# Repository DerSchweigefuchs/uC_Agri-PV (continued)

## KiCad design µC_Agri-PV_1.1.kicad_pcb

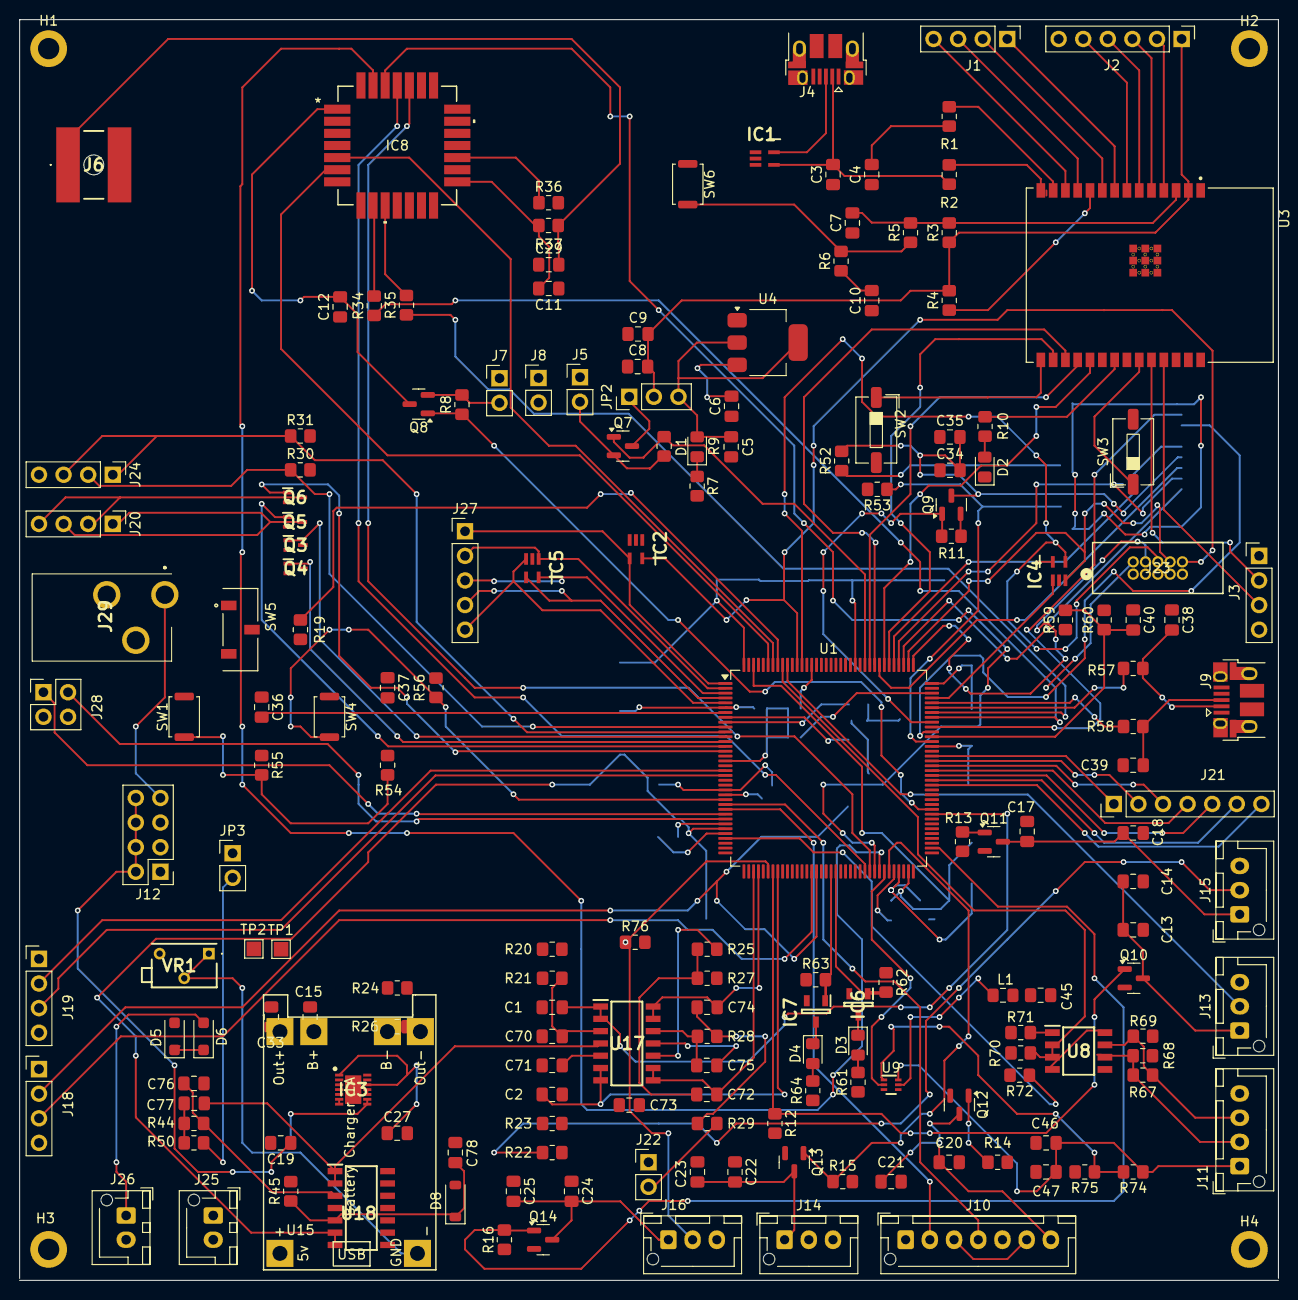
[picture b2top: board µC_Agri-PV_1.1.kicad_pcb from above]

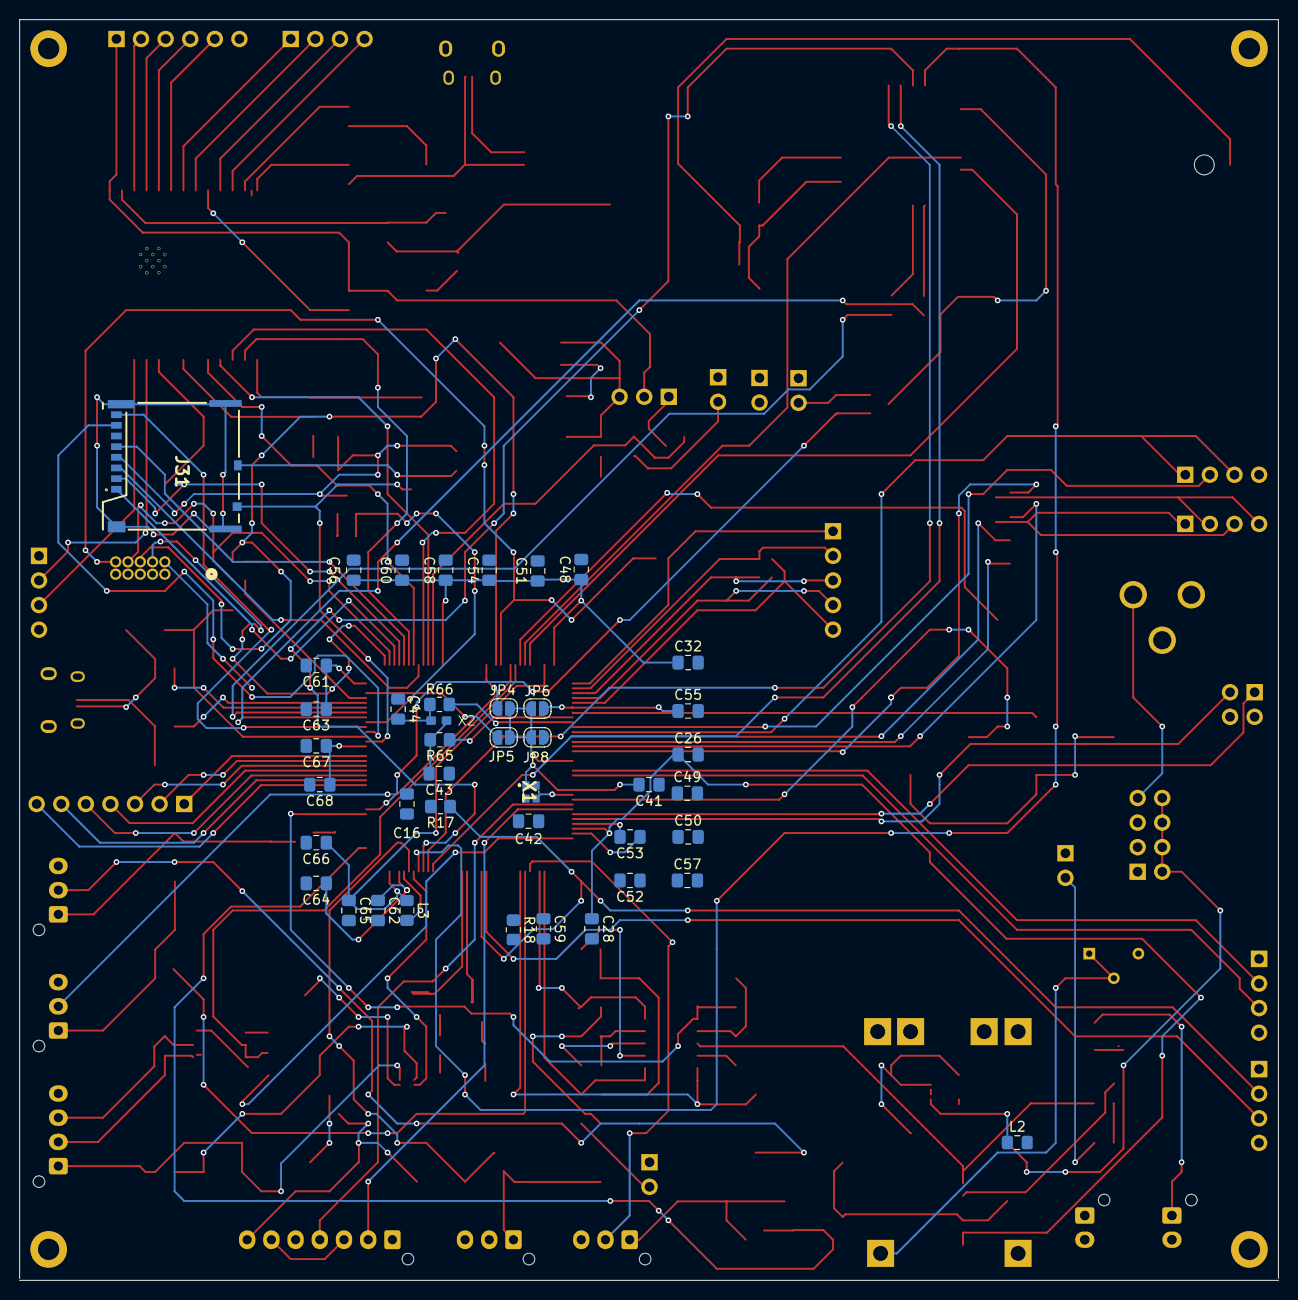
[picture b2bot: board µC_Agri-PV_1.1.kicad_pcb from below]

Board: 4 copper layers, 130.0 x 130.2 mm, 225 parts (42 on the bottom side), 184 nets.

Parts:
C1, C2, C72, C74, C77: 33n; C_0805_2012Metric_Pad1.18x1.45mm_HandSolder
C3, C4, C11, C29, C38, C39: TBD; C_0805_2012Metric_Pad1.18x1.45mm_HandSolder
C5, C6, C8, C13, C15, C17, C19, C20, C22, C24, C33, C34, C36, C46, C47: 22u; C_0805_2012Metric_Pad1.18x1.45mm_HandSolder
C7, C26, C52, C55, C62, C78: 1u; C_0805_2012Metric_Pad1.18x1.45mm_HandSolder
C9, C10, C14, C18, C21, C23, C25, C27, C28, C32, C35, C37, C48, C50, C51, C53, C54, C56, C57, C58, C59, C60, C61, C63, C64, C67, C68: 100n; C_0805_2012Metric_Pad1.18x1.45mm_HandSolder
C12: 4,7uF; C_0805_2012Metric_Pad1.18x1.45mm_HandSolder
C16: 4.7u; C_0805_2012Metric_Pad1.18x1.45mm_HandSolder
C40: 10p; C_0805_2012Metric_Pad1.18x1.45mm_HandSolder
C41, C42, C43, C44: 6.8pF; C_0805_2012Metric_Pad1.18x1.45mm_HandSolder
C45, C49: 10u; C_0805_2012Metric_Pad1.18x1.45mm_HandSolder
C65, C66: 2.2u; C_0805_2012Metric_Pad1.18x1.45mm_HandSolder
C70, C71, C73, C75, C76: 15n; C_0805_2012Metric_Pad1.18x1.45mm_HandSolder
D1, D2, D3, D4: LED; LED_0805_2012Metric_Pad1.15x1.40mm_HandSolder
D5, D6: D_Schottky; D_SOD-123F
D8: D_Zener; D_SOD-123
H1, H2, H3, H4: MountingHole_Pad; MountingHole_2.2mm_M2_DIN965_Pad
IC1, IC2, IC4, IC5: ESDALC6V1W5; SOT65P210X110-5N
IC3: TPS63021DSJR; SON50P300X400X100-15N-D
IC6, IC7: MMS9013-L-TP; SOT95P237X125-3N
IC8: 317990687; QFN_90687_SEE-M
J1, J3, J18, J19, J20, J24: Conn_01x04_Pin; PinHeader_1x04_P2.54mm_Vertical
J2: Conn_01x06_Pin; PinHeader_1x06_P2.54mm_Vertical
J4, J9: USB_B_Micro; USB_Micro-B_Amphenol_10103594-0001LF_Horizontal
J5, J7, J8, J22: Conn_01x02_Pin; PinHeader_1x02_P2.54mm_Vertical
J6: Conn_Coaxial; CONSMA001SMDGT
J10: Conn_01x07_Pin; JST_XH_B7B-XH-AM_1x07_P2.50mm_Vertical
J11: Conn_01x04_Pin; JST_XH_B4B-XH-AM_1x04_P2.50mm_Vertical
J12: Conn_02x04_Odd_Even; PinHeader_2x04_P2.54mm_Vertical
J13, J14, J15, J16: Conn_01x03_Pin; JST_XH_B3B-XH-AM_1x03_P2.50mm_Vertical
J21: Conn_01x07_Pin; PinHeader_1x07_P2.54mm_Vertical
J23: 3220-10-0100-00; CONN_3220-10-0100-00_CNC
J25, J26: Conn_01x02_Pin; JST_XH_B2B-XH-AM_1x02_P2.50mm_Vertical
J27: Conn_01x05_Pin; PinHeader_1x05_P2.54mm_Vertical
J28: Conn_02x02_Counter_Clockwise; PinHeader_2x02_P2.54mm_Vertical
J29: PJ-102B; PJ102B
J31: 503398-1892; 503398-1892-1
JP2: Jumper_3_Open; PinHeader_1x03_P2.54mm_Vertical
JP3: Jumper_2_Bridged; PinHeader_1x02_P2.54mm_Vertical
JP4, JP5, JP6, JP8: SolderJumper_2_Bridged; SolderJumper-2_P1.3mm_Open_RoundedPad1.0x1.5mm
L1, L2: 1u; L_0805_2012Metric_Pad1.15x1.40mm_HandSolder
L3: 2.2u; L_0805_2012Metric_Pad1.15x1.40mm_HandSolder
Q3, Q4, Q5, Q6: DMG1012T-13; SOT50P160X90-3N
Q7, Q8, Q9, Q10, Q11, Q12, Q13, Q14: IRLML6402; SOT-23
R1, R2, R5, R52, R57, R58, R65, R66: 0k; R_0805_2012Metric_Pad1.20x1.40mm_HandSolder
R3, R19, R70, R71, R72: 10k; R_0805_2012Metric_Pad1.20x1.40mm_HandSolder
R4, R8, R9, R11, R12, R13, R14, R15, R16, R53, R54, R62, R63, R75: 100k; R_0805_2012Metric_Pad1.20x1.40mm_HandSolder
R6, R7, R10, R20, R22, R27, R29, R45, R50, R55, R56, R61, R64: 1k; R_0805_2012Metric_Pad1.20x1.40mm_HandSolder
R17, R18, R30, R31: 2k2; R_0805_2012Metric_Pad1.20x1.40mm_HandSolder
R21, R23, R25, R28, R44: 2k; R_0805_2012Metric_Pad1.20x1.40mm_HandSolder
R24, R26, R59: 330k; R_0805_2012Metric_Pad1.20x1.40mm_HandSolder
R34, R35, R36: 22; R_0805_2012Metric_Pad1.20x1.40mm_HandSolder
R37: 0R; R_0805_2012Metric_Pad1.20x1.40mm_HandSolder
R60: 49k9; R_0805_2012Metric_Pad1.20x1.40mm_HandSolder
R67: 120; R_0805_2012Metric_Pad1.20x1.40mm_HandSolder
R68, R69: 20k; R_0805_2012Metric_Pad1.20x1.40mm_HandSolder
R74: 732k; R_0805_2012Metric_Pad1.20x1.40mm_HandSolder
R76: 4,7k; R_0805_2012Metric_Pad1.20x1.40mm_HandSolder
SW1, SW4, SW6: SW_Push; SW_Push_SPST_NO_Alps_SKRK
SW2, SW3: SW_DIP_x01; SW_DIP_SPSTx01_Slide_6.7x4.1mm_W6.73mm_P2.54mm_LowProfile_J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
SW5: SW_SPDT; SW_JS102011JCQN
TP1, TP2: TestPoint; TestPoint_Pad_1.5x1.5mm
U1: STM32U575ZIT6Q; LQFP-144_20x20mm_P0.5mm
U3: ESP32-C6-WROOM-1-N8; XCVR_ESP32-C6-WROOM-1-N8
U4: AMS1117-3.3; SOT-223-3_TabPin2
U8: ISL83078EIBZA; SOIC127P600X175-8N
U9: TPS61023DRLR; DRL0006A
U15: TP4056-18650
U17, U18: TLV9304IDR; SOIC127P600X175-14N
VR1: 3266X-1-203LF; 3266X1203LF
X1: XTAL_4_PINS; NX2016SA32MEXS00ACS06465
X2: XTAL_2_PINS; NX1610SE

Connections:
+3.3V: C15.1, C33.1, C45.2, IC3.3 (FB), IC3.4 (VOUT_1), IC3.5 (VOUT_2), J5.1, J7.1, J8.1, J18.4, J19.4, J23.1, J24.1, JP3.1 (A), L1.1, Q10.2 (S), Q11.2 (S), Q12.2 (S), Q13.2 (S), Q14.2 (S), R12.2, R13.2, R14.2, R15.2, R16.1, R17.2, R18.2, R30.2, R31.2, R45.2, R54.2, R61.1, R64.1, R68.1, R70.2, R71.2, R72.2, R76.2, SW5.1 (A), TP2.1, U8.8 (VCC), U9.3 (VIN), U18.4 (V+)
+BATT: J25.1, TP1.1, U15.5 (B+)
/ESP32-C6-WROOM-1-N8/11: J1.3, U3.11 (IO10)
/ESP32-C6-WROOM-1-N8/12: J1.4, U3.12 (IO11)
/ESP32-C6-WROOM-1-N8/EN: C7.2, R3.2, R5.2, U3.3 (EN)
/ESP32-C6-WROOM-1-N8/ESP32_EN: Q7.1 (G), R9.1, U1.119 (PD5)
/ESP32-C6-WROOM-1-N8/ESP32_MISO: U1.117 (PD3), U3.17 (IO19)
/ESP32-C6-WROOM-1-N8/ESP32_MOSI: U1.118 (PD4), U3.18 (IO20)
/ESP32-C6-WROOM-1-N8/ESP32_NSS: U1.114 (PD0), U3.16 (IO18)
/ESP32-C6-WROOM-1-N8/ESP32_SCK: U1.115 (PD1), U3.19 (IO21)
/ESP32-C6-WROOM-1-N8/VBus_ESP32: C6.2, J4.1 (VBUS), U4.3 (VI)
/ESP32-C6-WROOM-1-N8/Vdd: C8.2, C9.2, J2.1, J3.4, JP2.2 (C), R3.1, R4.2, U3.2 (3V3)
/IO and mounting holes/LED1: IC6.1 (B), R62.2, U1.56 (PE8)
/IO and mounting holes/LED2: IC7.1 (B), R63.2, U1.55 (PE7)
/IO and mounting holes/NRST: R56.2, SW4.2, U1.25 (NRST)
/IO and mounting holes/PC14-OSC32_IN: R65.1, U1.8 (PC14)
/IO and mounting holes/PC15-OSC32_OUT: R66.1, U1.9 (PC15)
/IO and mounting holes/PH0-OSC_IN: C41.2, U1.23 (PH0), X1.1
/IO and mounting holes/PH1-OSC_OUT: C42.2, U1.24 (PH1), X1.3
/IO and mounting holes/USB_D+: R58.2, U1.104 (PA12)
/IO and mounting holes/USB_D-: R57.2, U1.103 (PA11)
/IO and mounting holes/User_Button: C36.2, R55.1, U1.7 (PC13)
/IO and mounting holes/VBUS: J9.1 (VBUS), J12.3, R59.1
/IO and mounting holes/VBUS_SENSE: C40.2, R59.2, R60.1, U1.97 (PC7)
/LoRa-E5/LoRa_EN: Q8.1 (G), R8.1, U1.82 (PD13)
/LoRa-E5/MISO_LoRa: IC8.26 (PB14), U1.64 (PE14)
/LoRa-E5/MOSI_LoRa: IC8.27 (PA10), U1.65 (PE15)
/LoRa-E5/NRST2: R36.2, U1.85 (PD14)
/LoRa-E5/NSS_LoRa: IC8.25 (PB9), U1.62 (PE12)
/LoRa-E5/SCK_LoRa: IC8.24 (PB13), U1.63 (PE13)
/LoRa-E5/SCL_LoRa: IC8.5 (PB15), U1.138 (PB8)
/LoRa-E5/SDA_LoRa: IC8.6 (PA15), U1.139 (PB9)
/LoRa-E5/UART_RX: R35.1, U1.102 (PA10)
/LoRa-E5/UART_TX: R34.1, U1.101 (PA9)
/LoRa-E5/Vdd: C12.2, IC8.1 (VCC), Q8.3 (D)
/Micro SD-Card Reader 503398-1892/SD_CLK: J31.5 (CLK), U1.113 (PC12)
/Micro SD-Card Reader 503398-1892/SD_CMD: J31.3 (CMD), U1.116 (PD2)
/Micro SD-Card Reader 503398-1892/SD_DAT0: J31.7 (DAT0), U1.98 (PC8)
/Micro SD-Card Reader 503398-1892/SD_DAT1: J31.8 (DAT1), U1.99 (PC9)
/Micro SD-Card Reader 503398-1892/SD_DAT2: J31.1 (DAT2), U1.111 (PC10)
/Micro SD-Card Reader 503398-1892/SD_DAT3: J31.2 (CD/DAT3), U1.112 (PC11)
/Micro SD-Card Reader 503398-1892/SD_Detect: J31.9 (DETECT_LEVER), R53.1, U1.96 (PC6)
/Micro SD-Card Reader 503398-1892/SD_EN: Q9.1 (G), R11.1, U1.100 (PA8)
/Micro SD-Card Reader 503398-1892/Vdd: C34.2, C35.2, J31.4 (VDD), Q9.3 (D), R52.2
/Power Supply/VBat: C55.1, JP6.2 (B), U1.6 (VBAT)
/Power Supply/VBat_meas: R24.2, R26.1, U1.41 (PA6)
/Power Supply/VRefP: C26.1, C28.1, U1.31 (VREF+), U18.6 (IN_B), U18.7 (OUT_B)
/Power Supply/Vdd_Bat: D5.2 (A), J12.1, R24.1, U15.6 (Vcc_OUT)
/Power Supply/Vdd_Ext: D5.1 (K), D6.1 (K), J12.5
/Power Supply/Vdd_IO2: C67.1, C68.1, JP4.2 (B), U1.95 (VDDIO2), U1.130 (VDDIO2)
/Power Supply/Vdd_MCU: C16.1, C32.1, C48.1, C49.1, C50.1, C51.1, C54.1, C56.1, C57.1, C58.1, C60.1, C61.1, C63.1, JP3.2 (B), JP4.1 (A), JP5.1 (A), JP6.1 (A), JP8.1 (A), R50.1, U1.17 (VDD), U1.38 (VDD), U1.49 (VDD), U1.59 (VDD), U1.73 (VDD), U1.84 (VDD), U1.108 (VDD), U1.121 (VDD), U1.144 (VDD)
/Power Supply/Vdd_SMPS: C62.1, C64.1, JP8.2 (B), U1.69 (VDDSMPS)
/Power Supply/Vdd_USB: C59.1, JP5.2 (B), U1.106 (VDDUSB)
/STM32U575ZIT6Q/ADC4_IN9: C72.2, U1.39 (PA4), U17.8 (OUT_C), U17.9 (IN_C)
/STM32U575ZIT6Q/ADC4_IN10: C74.2, U1.40 (PA5), U17.13 (IN_D), U17.14 (OUT_D)
/STM32U575ZIT6Q/BME_EN: Q12.1 (G), R14.1, U1.75 (PB14)
/STM32U575ZIT6Q/DEBUG_JTCK: IC4.5 (I/04), J23.4, U1.109 (PA14)
/STM32U575ZIT6Q/DEBUG_JTDI: IC4.3 (I/02), J23.8, U1.110 (PA15)
/STM32U575ZIT6Q/DEBUG_JTDO: IC4.4 (I/03), J23.6, U1.132 (PB3)
/STM32U575ZIT6Q/DEBUG_JTMS: IC4.1 (I/01), J23.2, U1.105 (PA13)
/STM32U575ZIT6Q/DEBUG_JTRST: IC2.5 (I/04), J23.10, U1.133 (PB4)
/STM32U575ZIT6Q/DE/RE: R70.1, U1.136 (PB7), U8.2 (*RE), U8.3 (DE)
/STM32U575ZIT6Q/I2C3_SCL: J10.4, U1.26 (PC0)
/STM32U575ZIT6Q/I2C3_SDA: J10.2, U1.27 (PC1)
/STM32U575ZIT6Q/PAR_EN: U1.66 (PB10), U9.2 (EN)
/STM32U575ZIT6Q/Signal_UV_radiation: J15.2, R22.1
/STM32U575ZIT6Q/Signal_soil_moisture: J14.2, R20.1
/STM32U575ZIT6Q/Signal_wind_velocity: J13.2, U1.135 (PB6)
/STM32U575ZIT6Q/SoilMoist_EN: Q13.1 (G), R15.1, U1.67 (PB11)
/STM32U575ZIT6Q/SoilTemp_EN: Q14.1 (G), R16.2, U1.74 (PB13)
/STM32U575ZIT6Q/Soil_Moisture: C1.1, U1.81 (PD12), U17.1 (OUT_A), U17.2 (IN_A)
/STM32U575ZIT6Q/UART4_RX: R71.1, U1.34 (PA1), U8.1 (RO)
/STM32U575ZIT6Q/UART4_TX: R72.1, U1.33 (PA0), U8.4 (DI)
/STM32U575ZIT6Q/USART2_ONEWIRE: J16.2, R76.1, U1.42 (PA7)
/STM32U575ZIT6Q/UV_EN: Q11.1 (G), R13.1, U1.134 (PB5)
/STM32U575ZIT6Q/UV_Radiation: C2.1, U1.44 (PB1), U17.6 (IN_B), U17.7 (OUT_B)
/STM32U575ZIT6Q/Vdd_11: C65.1, C66.1, L3.1, U1.71 (VDD11), U1.142 (VDD11)
/STM32U575ZIT6Q/Wind_EN: Q10.1 (G), R12.1, U1.43 (PB0)
/Sensors/5V: C46.2, C47.2, J11.1, R74.1, U9.6 (VOUT)
GND: C3.1, C4.1, C5.1, C6.1, C7.1, C8.1, C9.1, C10.1, C11.1, C12.1, C13.1, C14.1, C15.2, C16.2, C17.1, C18.1, C19.2, C20.1, C21.1, C22.1, C23.1, C24.1, C25.1, C26.2, C27.2, C28.2, C29.1, C32.2, C33.2, C34.1, C35.1, C36.1, C37.1, C38.1, C39.1, C40.1, C41.1, C42.1, C43.1, C44.1, C45.1, C46.1, C47.1, C48.2, C49.2, C50.2, C51.2, C54.2, C55.2, C56.2, C57.2, C58.2, C59.2, C60.2, C61.2, C62.2, C63.2, C64.2, C65.2, C66.2, C67.2, C68.2, C76.2, C78.2, D2.1 (K), D8.2 (A), H1.1, H2.1, H3.1, H4.1, IC1.2 (GND), IC2.2 (GND), IC3.2 (GND), IC3.13 (PS/SYNC), IC3.15 (EP), IC4.2 (GND), IC5.2 (GND), IC6.2 (E), IC7.2 (E), IC8.2 (GND_1), IC8.14 (GND_2), IC8.16 (GND_3), IC8.22 (GND_4), J2.6, J3.1, J4.5 (GND), J6.2 (Ext), J9.5 (GND), J10.5, J11.4, J13.3, J14.3, J15.3, J16.3, J18.1, J19.1, J23.3, J23.5, J24.4, J25.2, J26.2, J28.3, J28.4, J29.2, J31.6 (VSS), Q3.2 (S), Q4.2 (S), Q5.2 (S), Q6.2 (S), R7.2, R26.2, R53.2, R60.2, R62.1, R63.1, R69.1, R75.2, SW1.2, SW2.2, SW3.2, SW4.1, SW5.3 (C), SW6.1, U1.16 (VSS), U1.37 (VSS), U1.48 (VSS), U1.58 (VSS), U1.70 (VSSSMPS), U1.72 (VSS), U1.83 (VSS), U1.94 (VSS), U1.107 (VSS), U1.120 (VSS), U1.129 (VSS), U1.143 (VSS), U3.1 (GND), U3.28 (GND), U3.30_1 (GND), U3.30_2 (GND), U3.30_3 (GND), U3.30_4 (GND), U3.30_5 (GND), U4.1 (GND), U8.5 (GND), U9.4 (GND), U15.1 (Vss_IN), U15.3 (Vss_OUT), U15.4 (B-), U18.11 (V), VR1.3 (CW), X1.2, X1.4
GNDA: C52.2, C53.2, C70.1, C71.2, C73.2, C75.1, U1.30 (VSSA), U17.11 (V)
unnamed: C1.2, R20.2, R21.1
unnamed: C2.2, R22.2, R23.1
unnamed: C10.2, R6.1
unnamed: C37.2, R56.1
unnamed: C72.1, R25.2, R27.1
unnamed: C74.1, R28.2, R29.1
unnamed: C77.1, R44.1, R50.2
unnamed: C5.2, D1.2 (A), JP2.3 (B), U4.2 (VO)
unnamed: D1.1 (K), R7.1
unnamed: D2.2 (A), R10.1
unnamed: D3.2 (A), R61.2
unnamed: D3.1 (K), IC6.3 (C)
unnamed: D4.2 (A), R64.2
unnamed: D4.1 (K), IC7.3 (C)
unnamed: D6.2 (A), J26.1
unnamed: C78.1, D8.1 (K), R45.1, U18.5 (+IN_B)
unnamed: C3.2, IC1.4 (I/03), J4.2 (D-), R2.2
unnamed: C4.2, IC1.5 (I/04), J4.3 (D+), R1.2
unnamed: IC2.4 (I/03), J27.1, U1.1 (PE2)
unnamed: C27.1, IC3.1 (VINA), IC3.12 (EN)
unnamed: IC3.8 (L1_1), IC3.9 (L1_2), L2.1
unnamed: IC3.6 (L2_1), IC3.7 (L2_2), L2.2
unnamed: C19.1, IC3.10 (VIN_1), IC3.11 (VIN_2), J12.2, J12.4, J12.6, J12.8
unnamed: IC5.1 (I/01), J27.2, U1.2 (PE3)
unnamed: IC5.3 (I/02), J27.5, U1.5 (PE6)
unnamed: IC5.4 (I/03), J27.4, U1.4 (PE5)
unnamed: IC5.5 (I/04), J27.3, U1.3 (PE4)
unnamed: IC8.10 (PB6), R35.2
unnamed: IC8.9 (PB7), R34.2
unnamed: C11.2, IC8.15 (RFIO), R37.1
unnamed: IC8.17 (RST), R36.1
unnamed: J1.1, U3.8 (IO0)
unnamed: J1.2, U3.9 (IO1)
unnamed: J2.2, U3.4 (IO4)
unnamed: J2.3, U3.5 (IO5)
unnamed: J2.4, U3.6 (IO6)
unnamed: J2.5, U3.7 (IO7)
unnamed: J3.2, U3.24 (RXD0/GPIO17)
unnamed: J3.3, U3.25 (TXD0/GPIO16)
unnamed: J5.2, Q7.2 (S), R9.2
unnamed: C29.2, J6.1 (In), R37.2
unnamed: J7.2, Q8.2 (S), R8.2
unnamed: J8.2, Q9.2 (S), R11.2
unnamed: C39.2, J9.3 (D+), R58.1
unnamed: C38.2, J9.2 (D-), R57.1
unnamed: J10.3, J10.6
unnamed: C20.2, C21.2, J10.7, Q12.3 (D)
unnamed: J11.2, R67.1, R68.2, U8.6 (A/Y)
unnamed: J11.3, R67.2, R69.2, U8.7 (B/Z)
unnamed: J12.7, J29.1
unnamed: C13.2, C14.2, J13.1, Q10.3 (D)
unnamed: C22.2, C23.2, J14.1, Q13.3 (D)
unnamed: C17.2, C18.2, J15.1, Q11.3 (D)
unnamed: C24.2, C25.2, J16.1, Q14.3 (D)
unnamed: J18.2, R17.1, U1.52 (PF15)
unnamed: J18.3, R18.1, U1.51 (PF14)
unnamed: J19.2, U1.19 (PF7)
unnamed: J19.3, U1.20 (PF8)
unnamed: J20.1, Q3.3 (D)
unnamed: J20.2, Q4.3 (D)
unnamed: J20.3, Q5.3 (D)
unnamed: J20.4, Q6.3 (D)
unnamed: J21.1, U1.93 (PG8)
unnamed: J21.2, U1.92 (PG7)
unnamed: J21.3, U1.91 (PG6)
unnamed: J21.4, U1.90 (PG5)
unnamed: J21.5, U1.89 (PG4)
unnamed: J21.6, U1.88 (PG3)
unnamed: J21.7, U1.87 (PG2)
unnamed: J22.1, R27.2
unnamed: J22.2, R29.2
unnamed: J24.2, R30.1, U1.10 (PF0)
unnamed: J24.3, R31.1, U1.11 (PF1)
unnamed: J28.1, U1.28 (PC2)
unnamed: J28.2, U1.29 (PC3)
unnamed: J31.10 (DETECT_SWITCH), R52.1
unnamed: JP2.1 (A), Q7.3 (D)
unnamed: Q3.1 (G), U1.12 (PF2)
unnamed: Q4.1 (G), U1.13 (PF3)
unnamed: Q5.1 (G), U1.14 (PF4)
unnamed: Q6.1 (G), U1.15 (PF5)
unnamed: R5.1, R6.2, SW6.2
unnamed: R54.1, R55.2, SW1.1
unnamed: R19.1, SW5.2 (B)
unnamed: R19.2, U1.137 (PH3)
unnamed: L3.2, U1.68 (VLXSMPS)
unnamed: R4.1, U3.10 (IO8)
unnamed: SW2.1, U3.15 (IO9)
unnamed: R1.1, U3.13 (IO12)
unnamed: R2.1, U3.14 (IO13)
unnamed: SW3.1, U3.23 (IO15)
unnamed: R10.2, U3.21 (IO23)
unnamed: R74.2, R75.1, U9.1 (FB)
unnamed: L1.2, U9.5 (SW)
unnamed: U15.2 (R_trim), VR1.1 (CCW), VR1.2 (WIPER)
unnamed: C70.2, R21.2, U17.3 (+IN_A)
unnamed: C71.1, R23.2, U17.5 (+IN_B)
unnamed: C73.1, R25.1, U17.10 (+IN_C)
unnamed: C75.2, R28.1, U17.12 (+IN_D)
unnamed: C76.1, R44.2, U18.3 (+IN_A)
unnamed: C44.2, R66.2, X2.1 (X1)
unnamed: C43.2, R65.2, X2.2 (X2)
VDDA: C52.1, C53.1, C77.2, U1.32 (VDDA), U17.4 (V+), U18.1 (OUT_A), U18.2 (IN_A)

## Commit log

2025-12-17 Incorporation of the project of the predecessor of revision v1.1
2025-12-17 Add FC0V104ZFTBR24 component library files
    Added symbol, footprint, 3D model, and documentation files for the Supercap (FC0V104ZFTBR24) component across multiple EDA tool formats. Also updated schematic files and project backups, and removed 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
2025-12-18 Add TP4056-18650 footprint and update Power schematic
    Added the TP4056-18650-2 footprint to the library and assigned it to the battery charger in Power.kicad_sch. Updated the Power schematic to improve symbol details, add descriptive properties, and enh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
2025-12-18 Update schematic and PCB version to 1.3, update dates
    Updated revision numbers and dates to 2025-12-18 (version 1.3) across all KiCad schematic files and the PCB. Adjusted the board text to reflect the new version and date. Also updated backup ZIP file 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
2025-12-18 Add .gitignore for backups and remove backup zip
    Added .gitignore to exclude the µC_Agri-PV-backups directory from version control and deleted an existing backup zip file from the repository.
2025-12-18 Add CHANGELOG.md and update .gitignore
    Added a CHANGELOG.md file documenting changes in version 1.3 and updated .gitignore to exclude .lck files.
2026-01-08 new layout
    - recreation of the layout
    - changed connection of ADC to MCU
    - cleaner layout
    - battery (supercap) for rtc
    - crystal nearby the mcu
    - 3V3 layer can be switched on/off separated from the mcu
2026-01-08 step file for Lora E5 module
2026-01-08 Update schematics to revision 2.0 and adjust Micro-SD layout
    Bump revision and date to 2.0 (2026-01-08) in all schematic sheets. Adjust wire and label positions in Micro-SD.kicad_sch and update R502 reference/value locations. Regenerate iBOM HTML.
2026-01-08 Add new ECAD part library files for 317990687
    Added multiple ECAD model files, 3D STEP file, documentation, and part information for component 317990687 across various EDA tool formats. Also removed auto-saved and backup files related to sensors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
2026-01-08 Add free via at (33, 75) on PCB layout
    Inserted a new free via with 2mm size and 1.8mm drill at coordinates (33, 75) in the uC_Agri-PV.kicad_pcb file. Updated the .kicad_prl file to reflect changes in active and visible layers.
2026-01-09 Add v2.0 redesign files and documentation
    Introduced a complete hardware redesign for the uC_Agri-PV board (v2.0), including new KiCad PCB layout, updated schematic, and new documentation files: README.md, HARDWARE_PINOUT.md, and updated CHA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
2026-01-09 Clean up ignored files and update documentation
    Removed .DS_Store, KiCad backup, and autosave files from the repository. Expanded .gitignore to cover KiCad, OS, IDE, and temporary files. Updated CHANGELOG.md to English for v2.0 and improved clarit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
2026-01-10 Remove unnecessary files from tracking and update .gitignore
    - Remove backup files (*.kicad_sch-bak, *-backups/)
    - Remove autosave files (*_autosave*)
    - Remove local settings (*.kicad_prl)
    - Remove OS system files (.DS_Store)
    - Update .gitignore to prevent future tracking
2026-01-10 Update README BOM link and regenerate ibom.html
    Changed the Interactive BOM link in README.md to point to the hosted GitHub Pages version. Regenerated bom/ibom.html and updated uC_Agri-PV.kicad_pro, likely reflecting recent board or BOM changes.
2026-01-10 Update sensor table and version info in docs
    Revised the sensor table in README.md to reflect updated interfaces and removed the connector column. Updated version dates and notes in CHANGELOG.md for clarity. Also made minor corrections to docum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
2026-01-12 Add power control documentation and update image paths
    Introduced POWER_CONTROL.md with detailed board power management instructions. Updated README.md to reference the new documentation and moved image files to the images/ directory, adjusting paths acc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
2026-01-12 Update hardware docs: clarify power lanes and enable signals
    Added diagram and detailed explanation of 3.3V lane control in POWER_CONTROL.md, including new image. Updated HARDWARE_PINOUT.md to clarify that all enable signals are active LOW and corrected the en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
2026-01-14 Update wind speed sensor to digital frequency input
    Revised HARDWARE_PINOUT.md to reflect the change from RS485 (UART4) to a digital frequency input (TIM4_CH1) for the wind speed sensor (SEN0170), including updated pin assignments and data flow. Modif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
2026-01-14 Document power supply chain and add circuit diagrams
    Expanded POWER_CONTROL.md to describe the two-stage power architecture using TP4056 and TPS63021 components. Added circuit diagrams for the battery charger and buck-boost converter to the images dire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
2026-01-14 Update V2_0_Pin_definition.png image
    Replaces the existing V2_0_Pin_definition.png with a new version. This may reflect updated pin definitions or improved image clarity.
2026-01-20 Zwei falsche Vias (Achtung Kurzschluss) entfernt und Beschriftung STM-UART Stiftleisten und USB-Anschlüsse angepasst
2026-01-20 Änderung Beschriftungen und Drehung X8 (3V3 gleich zu X7)
2026-01-22 Änderungen an Bauteilbezeichnungen (nur optisch, nicht technisch) Bestellung PCB Jan 26 MultiCP
2026-03-05 Add board housing STEP files; update KiCad files
    Add exported mechanical STEP models for the board housing (CAD/board_housing.step and variants _o, _stg, _u). Also update KiCad project assets and documentation: POWER_CONTROL.md, Power.kicad_sch, ST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
2026-03-06 Update KiCad netlist and project prefs
    In the .net file update source path, tool version and dates/timestamps, add/modify components (add C2, R15; change part numbers/footprints/datasheets), remove some connector entries, and add procurem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
2026-06-25 Add SamacSys & CAPPRD library; update KiCad
    Add a new SamacSys parts library and a complete CAPPRD500 footprint/package set (870585375004) with multi-EDA exports and 3D STEP models. Also add sym-lib-table and SamacSys parts entries, and update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
